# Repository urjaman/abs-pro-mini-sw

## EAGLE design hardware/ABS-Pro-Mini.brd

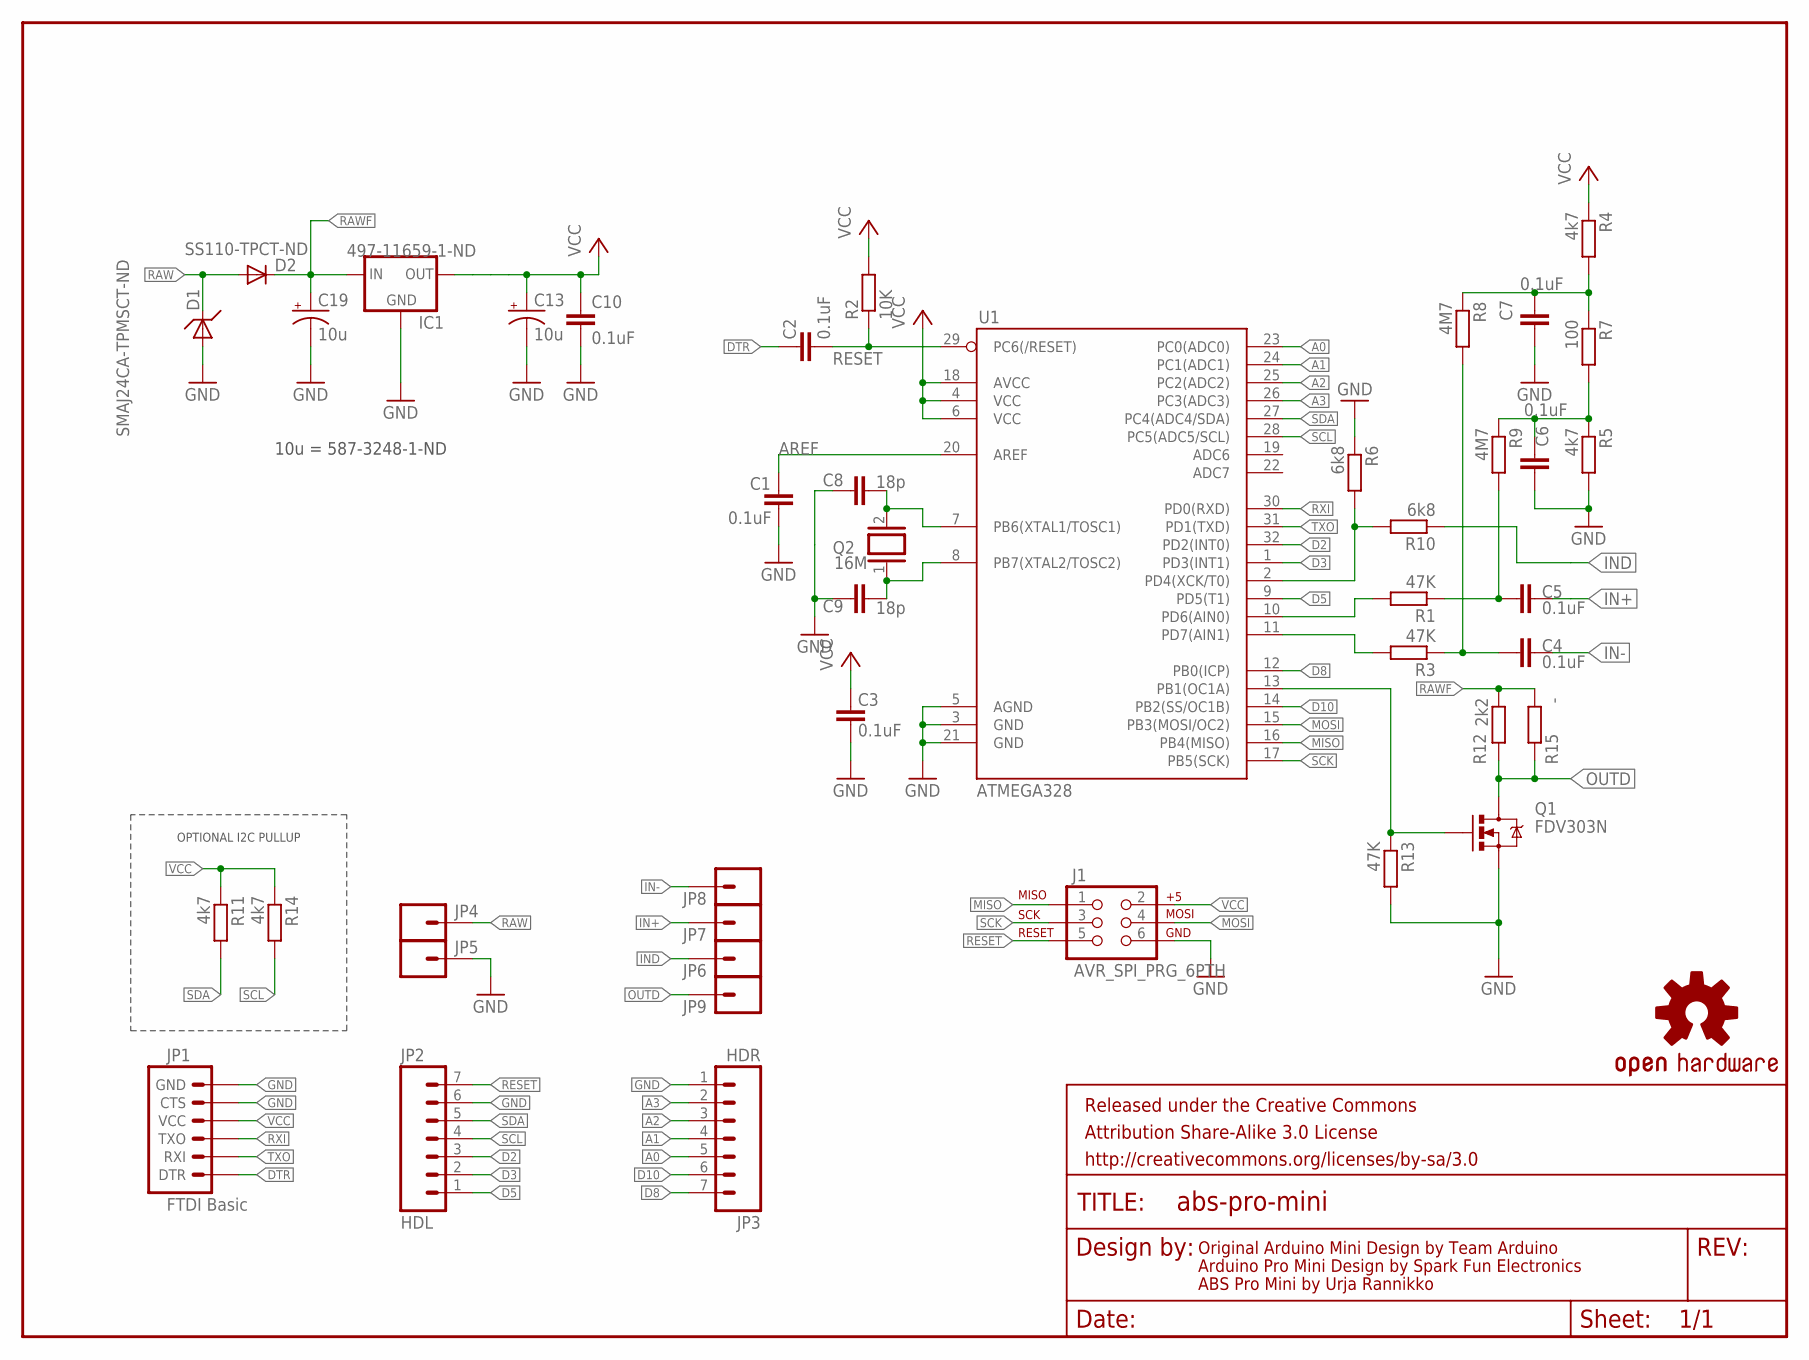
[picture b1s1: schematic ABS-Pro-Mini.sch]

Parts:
C1, C2, C3, C4, C5, C6, C7, C10: 0.1uF; 0603-CAP
C8, C9: 18p; 0603-CAP
C13, C19: 10u; EIA3216
D1: SMAJ24CA-TPMSCT-ND; SMA-DIODE
D2: SS110-TPCT-ND; SMA-DIODE
FRAME1: FRAME-LETTER; CREATIVE_COMMONS
IC1: 497-11659-1-ND; SOT223
J1: AVR_SPI_PRG_6PTH; 2X3
JP1: FTDI Basic; 1X06
JP2: HDL; 1X07
JP3: HDR; 1X07
JP4, JP5, JP6, JP7, JP8, JP9: M01PTH_2MM; 1X01_2MM
Q1: FDV303N; SOT23
Q2: 16M; QS
R1, R3, R13: 47K; R0805
R2: 10K; R0805
R4, R5, R11, R14: 4k7; R0805
R6, R10: 6k8; R0805
R7: 100; R0805
R8, R9: 4M7; 0207/12
R12: 2k2; R0805
R15: -; R0805
U1: ATMEGA328; TQFP32-08
U$3: OSHW-LOGOS; OSHW-LOGO-S

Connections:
A0: JP3.5, U1.23 (PC0(ADC0))
A1: JP3.4, U1.24 (PC1(ADC1))
A2: JP3.3, U1.25 (PC2(ADC2))
A3: JP3.2, U1.26 (PC3(ADC3))
AREF: C1.2, U1.20 (AREF)
BIASH: C7.1, R4.2, R7.1, R8.1
BIASL: C6.1, R5.1, R7.2, R9.1
CIN+: C5.2, R1.1, R9.2
CIN-: C4.2, R3.1, R8.2
D2: JP2.3, U1.32 (PD2(INT0))
D3: JP2.2, U1.1 (PD3(INT1))
D5: JP2.1, U1.9 (PD5(T1))
D8: JP3.7, U1.12 (PB0(ICP))
D10: JP3.6, U1.14 (PB2(SS/OC1B))
DIN+: R1.2, U1.10 (PD6(AIN0))
DIN-: R3.2, U1.11 (PD7(AIN1))
DTR: C2.2, JP1.1 (DTR)
GND: C1.1, C3.1, C6.2, C7.2, C8.2, C9.2, C10.2, C13.C (-), C19.C (-), D1.A, IC1.2 (GND), IC1.4 (GND), J1.6, JP1.5 (CTS), JP1.6 (GND), JP2.6, JP3.1, JP5.1, Q1.2 (S), R5.2, R6.1, R13.2, U1.3 (GND), U1.5 (AGND), U1.21 (GND)
IN+: C5.1, JP7.1
IN-: C4.1, JP8.1
IND: JP6.1, R10.1
INDLV: R6.2, R10.2, U1.2 (PD4(XCK/T0))
MISO: J1.1, U1.16 (PB4(MISO))
MOSI: J1.4, U1.15 (PB3(MOSI/OC2))
unnamed: C9.1, Q2.1, U1.8 (PB7(XTAL2/TOSC2))
unnamed: C8.1, Q2.2, U1.7 (PB6(XTAL1/TOSC1))
OUTD: JP9.1, Q1.3 (D), R12.2, R15.2
OUTD_CTRL: Q1.1 (G), R13.1, U1.13 (PB1(OC1A))
RAW: D1.C, D2.A, JP4.1
RAWF: C19.A (+), D2.C, IC1.1 (IN), R12.1, R15.1
RESET: C2.1, J1.5, JP2.7, R2.1, U1.29 (PC6(/RESET))
RXI: JP1.3 (TXO), U1.30 (PD0(RXD))
SCK: J1.3, U1.17 (PB5(SCK))
SCL: JP2.4, R14.2, U1.28 (PC5(ADC5/SCL))
SDA: JP2.5, R11.2, U1.27 (PC4(ADC4/SDA))
TXO: JP1.2 (RXI), U1.31 (PD1(TXD))
VCC: C3.2, C10.1, C13.A (+), IC1.3 (OUT), J1.2, JP1.4 (VCC), R2.2, R4.1, R11.1, R14.1, U1.4 (VCC), U1.6 (VCC), U1.18 (AVCC)

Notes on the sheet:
Original Arduino Mini Design by Team Arduino
Arduino Pro Mini Design by Spark Fun Electronics
10u = 587-3248-1-ND
ABS Pro Mini by Urja Rannikko
OPTIONAL I2C PULLUP

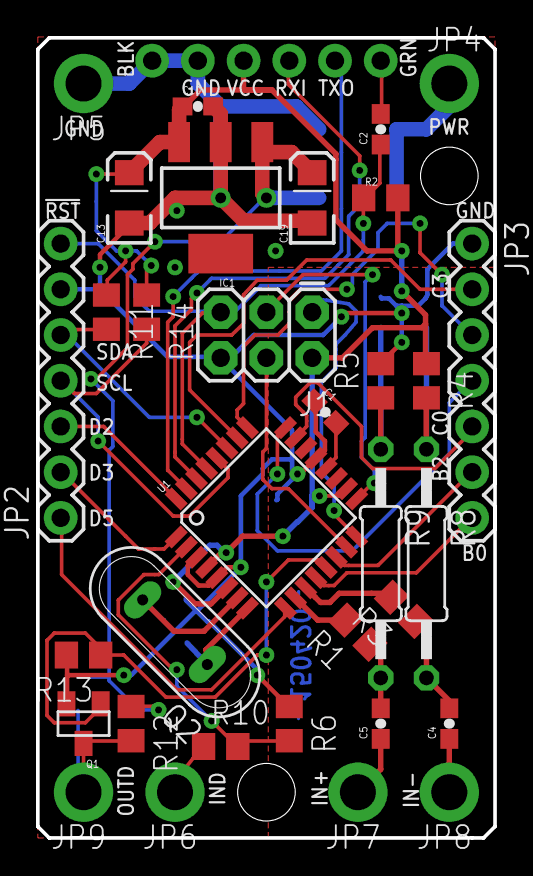
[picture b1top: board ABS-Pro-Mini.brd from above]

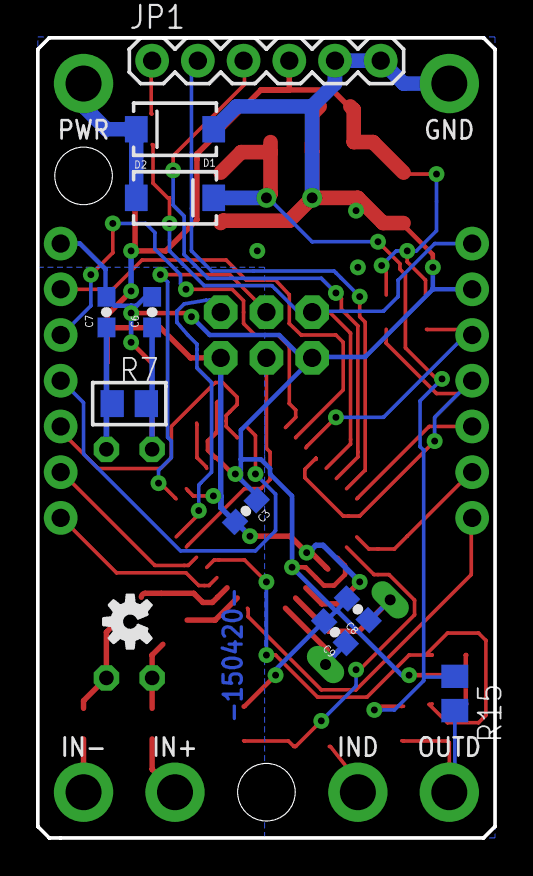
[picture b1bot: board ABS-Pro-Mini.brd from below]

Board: 2 copper layers, 25.4 x 44.5 mm, 45 parts (11 on the bottom side), 37 nets.

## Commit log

2015-04-26 Pre-hardware SW... (seems to run on my uno+ftdi-clone thing)
2015-04-27 Add hardware files
2015-04-27 upto-date schematic picture with proper values
2015-05-13 Add bootloader binary plus initial loading instructions ...
    and information on what the sources were, i dont want to
    copy the whole of optiboot here...
2015-05-13 maybe closer to proper rescaling factors for real use
2015-05-14 cleanup ifdefs for input digital
2015-05-14 bugfix for the arduino 1.6.3 environment ...
    it goofs something up but this workarounds it
2015-05-14 assorted useless stuff

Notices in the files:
parts and their libraries:
SparkFun-Aesthetics: Licensing: CC v3.0 Share-Alike You are welcome to use this library for commercial purposes.
SparkFun-Aesthetics: Released under the Creative Commons Attribution Share-Alike 3.0 License
SparkFun-Aesthetics: http://creativecommons.org/licenses/by-sa/3.0
